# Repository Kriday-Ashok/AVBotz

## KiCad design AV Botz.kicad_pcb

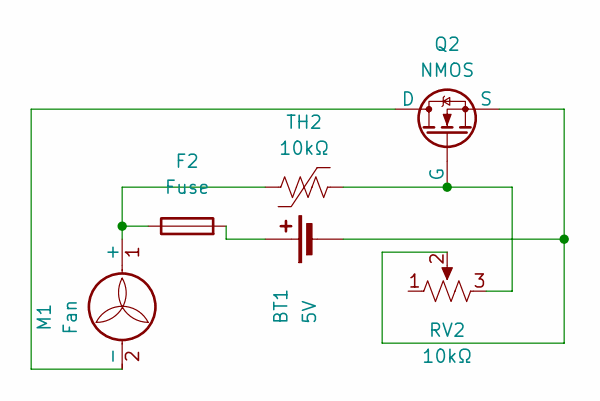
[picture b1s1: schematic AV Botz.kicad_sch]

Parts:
BT1: 5V; BatteryHolder_MPD_BC2AAPC_2xAA
F2: Fuse; Fuse_0402_1005Metric_Pad0.77x0.64mm_HandSolder
M1: Fan; LED_D3.0mm_Horizontal_O1.27mm_Z2.0mm_Clear
Q2: NMOS; TO-220F-3_Vertical
RV2: 10kΩ; Potentiometer_Bourns_3296P_Horizontal
TH2: 10kΩ; R_0805_2012Metric_Pad1.20x1.40mm_HandSolder

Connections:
unnamed: BT1.1 (+), F2.2
unnamed: BT1.2 (-), Q2.3 (S), RV2.2
unnamed: F2.1, M1.1 (+), TH2.1
unnamed: M1.2 (-), Q2.1 (D)
unnamed: Q2.2 (G), RV2.3, TH2.2

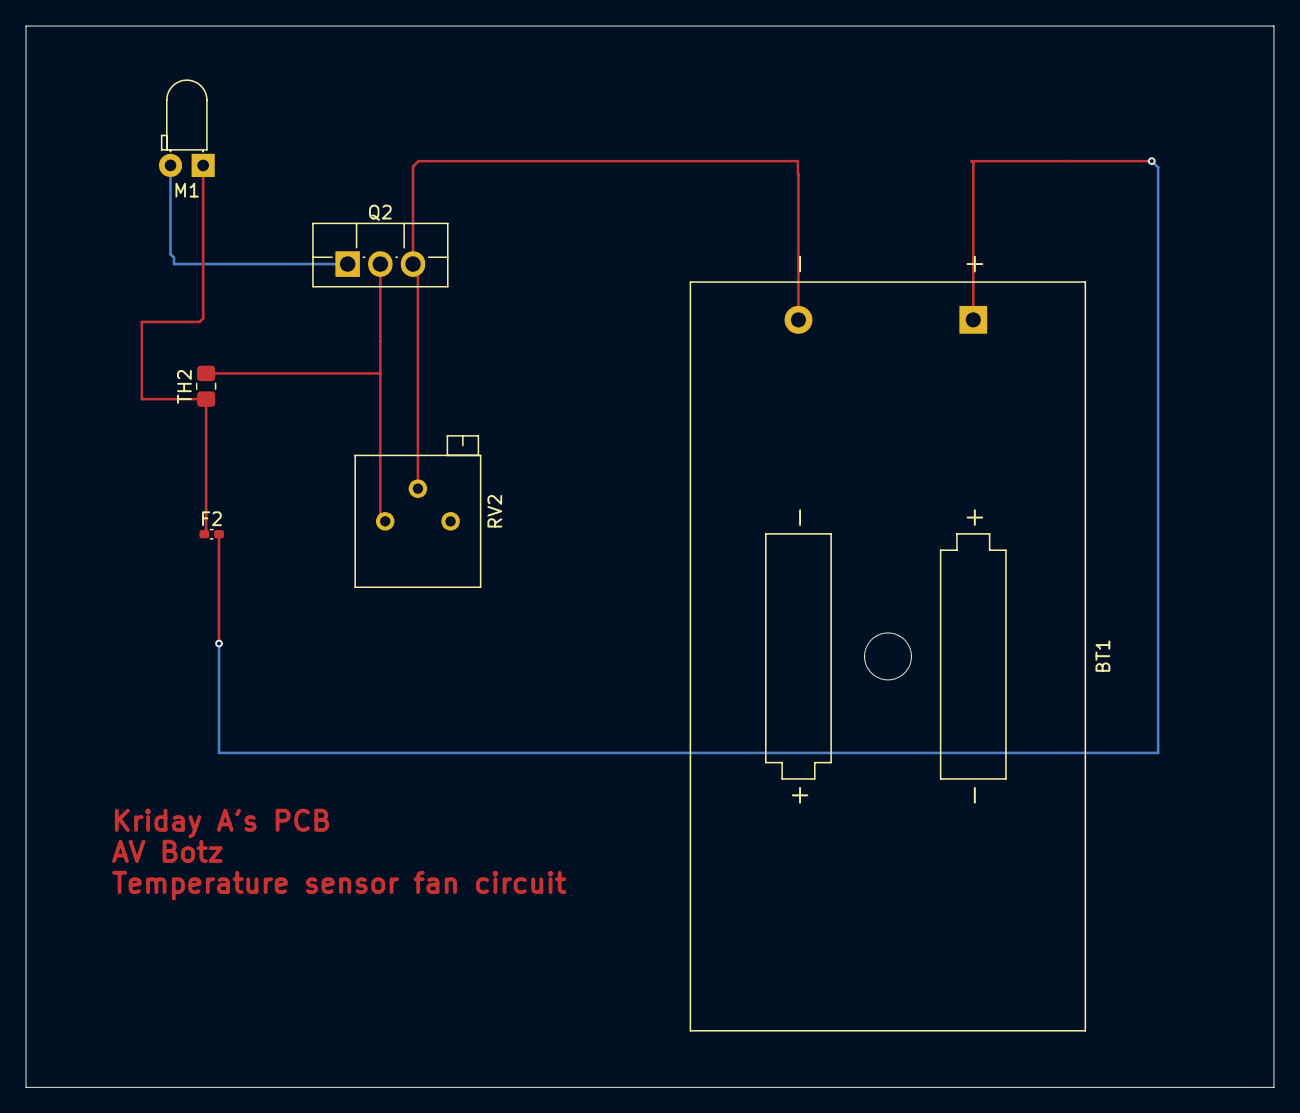
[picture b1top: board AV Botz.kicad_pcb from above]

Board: 2 copper layers, 97.0 x 82.5 mm, 6 parts (0 on the bottom side), 5 nets.

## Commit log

2025-09-15 Adding Zip
2025-09-15 Updated new Zip
